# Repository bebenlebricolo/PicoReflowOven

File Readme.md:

# Pico Reflow Oven

My own version of a custom reflow oven, built around my former kitchen oven and whatever was in
the drawers. Hence the "frankenstein" style: this time I'm not sourcing components for a project,
I'm building one from spare parts (plus a few things I still had to order).

I also reused a daughter board from a previous HV project ([NanoFridgeThermostat](https://github.com/bebenlebricolo/NanoFridgeThermostat)),
since it was designed as a self-contained opto-isolated triac switching board. A revisited
schematic for this project lives in `Electronics/PicoReflowOven/`.

## What is it for?

Reflowing custom PCBs in a 1500 W / 230 V convection oven that already has a high-temperature fan
and 2 sets of heating elements (top + bottom) — forced convection keeps the heat distribution as
even as possible.

- **Main target:** low-temp paste **Sn42Bi58** (melts at 138 °C, peak 170–180 °C)
- **Secondary target:** standard **SAC305 / SnAgCu** (peak ~245–250 °C) — reachable by
  disconnecting the original thermal cutout, in "bench" mode only (see Safety)

The stock oven dial goes to ~230 °C but only ever reached ~190–200 °C; measured ramp is
~0.6–0.67 °C/s, and the real fight is the **overshoot at the peak**, not the climb. Full analysis:
`Docs/DesignDeepDive.md`.

## Philosophy

Reuse parts, and keep the oven revertible to its stock configuration with minimal modifications
(original front panel and controls stay; a 2-pin connector restores the stock wiring in ~30 s).
Based on the stock configuration alone, low-temp paste is already reachable — what was missing is
a live temperature reading, a way to switch the elements, and an alarm to open the door.

## Safety (summary — the full architecture is part of the design, don't bypass it)

This project switches mains AC (230 V). Never touch live components. **No fuse, no thermal fuse**
(a shorted triac draws the same current as the load — no fuse would see it), so bounding is:

1. **Autonomous mode (SnBi only, default):** the original thermal cutout stays in series
   (~210–220 °C, above the 180 °C SnBi peak, independent of the Pico and triac). It trips below
   the SAC peak — SnBi only.
2. **Bench mode (any SAC run or test > 250 °C, cutout disconnected):** operator present at all
   times, mechanical timer armed, logical cutoffs ~300 °C.
3. **Mechanical timer armed at every run.** After every bench session, physically reconnect the
   cutout before any SnBi run. **SAC = bench mode only.**
4. House rules: thermal checks unplugged at residual heat; no PVC/thermoplastics in the cavity
   gap; HV/LV ≥ 6 mm apart in the enclosure; sacrificial probe bolted through a drilled FR4 plate.

Details: `Docs/DesignDeepDive.md` §3.

## Architecture — 3 layers, one golden rule

**The control loop and all safety mechanisms live on the Pico — the PC never supervises the hot
chain.** A run in progress survives a USB disconnect; PC/Bluetooth links are passive observers
(telemetry, settings, launch). Link loss mid-run = the run continues.

```
┌─────────────────────────────────────────────┐
│  Layer 3 — Local HMI                        │
│  SSD1306 OLED 128×64 + rotary encoder       │
│  + 2 buttons (Edit / Back)                  │
├─────────────────────────────────────────────┤
│  Layer 2 — USB protocol (CDC /dev/ttyACM0)  │
│  Commands: PROFILE, START, ABORT, GAINS,    │
│  MODE MANUAL x% · Telemetry CSV 1 Hz        │
├─────────────────────────────────────────────┤
│  Layer 1 — Autonomous control + safety      │
│  State machine RAMP/SOAK/PEAK/COOL/ALARM    │
│  PID 1 Hz on board probe · slow PWM         │
│  Interlocks, logical cutoffs                │
└─────────────────────────────────────────────┘
```

Layer 1 runs standalone (no PC, no HMI needed). Hardware, pinout (reference: the KiCad schematic),
measurement and protocol specs: `Docs/DesignDeepDive.md` and `Firmware/Readme.md`.

## Profiles

**SnBi first — the daily driver:**

| Phase | Setpoint |
|-------|----------|
| Free ramp | ~0.6 °C/s up to ~145 °C |
| Soak | 145–150 °C, 60–90 s |
| Peak | 170–180 °C |
| TAL | 30–60 s above 138 °C |
| Cooling | Door open + convection fan |

**SAC305 — later, bench mode only** (values [DATASHEET]): free ramp ~1–2 °C/s target to ~150 °C,
soak 150–180 °C 60–120 s, peak 245–250 °C, TAL 30–60 s above 217 °C, same cooling.

The profile table is extensible (paste alloy × board thermal mass) — not a hard-coded list.

## Using it

- **From the box:** OLED + encoder + Edit/Back. Edit = validate/START, Back = cancel; once
  running, the field becomes STOP and either button stops immediately.
- **From a Linux PC:** `/dev/ttyACM0` (native CDC, no reset on open — capture can start mid-cycle).
  Line protocol: `PROFILE <name>`, `START`, `ABORT`, `GAINS kp ki kd`, `MODE MANUAL x%`;
  1 Hz CSV telemetry `t,sp,tc_board,tc_air,duty,STATE` (e.g. `cat /dev/ttyACM0 | tee run.csv`).
  Group `dialout`; disable ModemManager. Nothing is logged before the port is opened. Spec:
  `Firmware/Readme.md`.
---

## Repo layout

```
PicoReflowOven/
├── Readme.md                  ← you are here
├── AGENTS.md                  ← rules for AI agents working in this repo
├── Docs/
│   ├── InitialContext.md      ← full project write-up (Nov 2026, FR) — decision source of truth
│   └── DesignDeepDive.md      ← technical deep dive (oven analysis, safety, pinout, protocol…)
├── Electronics/
│   ├── Readme.md              ← HT daughter board, triac, wiring, BOM
│   └── PicoReflowOven/        ← KiCad schematic + PCB (pinout reference)
└── Firmware/
    └── Readme.md              ← firmware layers, pinout, USB protocol
```

## Where we're at (Nov 2026)

- [x] Design frozen (safety architecture, triac choice, pinout per KiCad schematic)
- [ ] Wiring the power section + protections
- [ ] Firmware generation (layer 1 → 2 → 3)
- [ ] No-load runs (`MODE MANUAL 100` 20–30 min → unplugged thermal check → heatsink ≤ 70 °C)
- [ ] Calibration (probe in 3 positions), profile runs with PC plot, PID tuning
- [ ] First real reflow, logged

Still [OPEN]: SAC ramp near 250 °C (measure on first bench run) · SAC bench-only decision to be
logged as DEC-XXX · TME delivery checks (Kapton adhesive = silicone, TKD wire ≥ 1 mm², triac =
BTA316Y) · blower-on-cutout idea under exploration (see `Docs/DesignDeepDive.md` §1.1).

Later, maybe: re-insulate with rock wool (encapsulated) for a faster ramp and higher ceiling.

## Disclaimer

This thing plugs into the wall (230 V) and runs hot. Build at your own risk — the safety
architecture above is part of the design, don't bypass it.

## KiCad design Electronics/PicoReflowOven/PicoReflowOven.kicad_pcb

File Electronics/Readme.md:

# Electronics

This folder is the home of the Electronics designs (schematics, PCBs, BOM, wiring).

The low-voltage control board schematic lives in [`PicoReflowOven/PicoReflowOven.kicad_sch`](PicoReflowOven/PicoReflowOven.kicad_sch) (KiCad 10) — it is the **as-built source of truth for the pinout** (see the pinout tables in the root `Readme.md` and `Firmware/Readme.md`). Regenerate the netlist with `kicad-cli sch export netlist`.

The power section reuses a daughter board from the **NanoFridgeThermostat** project and drives a **230 V / 1500 W** convection oven through a triac. All design decisions below are frozen — see `Docs/InitialContext.md` for the full rationale.

---

## HT Daughter Board (reused from NanoFridgeThermostat)

Reusing the HT Daughter board from [NanoFridgeThermostat:](https://github.com/bebenlebricolo/NanoFridgeThermostat)
| Item | Value |
|------|-------|
| Opto-triac | **MOC3042M** (zero-cross detection built in) |
| Snubber | R4 360 Ω + C1 10 nF / 500 V AC |
| Terminals | TE 5.08 mm |
| Headers | J5 = `TriacDriverEnable`, J6 = LED return (2.54 mm) |
| R8 | 330 Ω (unchanged — design point: limits MOC peak current to 1 A) |

**J6 is no longer ground** — it is the switched LED return. At rest, J6 measures ~5 V; that is normal, not a fault.

---

## Triac

| | Phase 1 (validation only) | Final |
|---|---|---|
| Part | FT0814MH | **BTA316Y-800CTQ** (WeEn) |
| Rating | 8 A / 600 V, bare tab | 16 A / 800 V, **IITO-220 factory-isolated tab** (2500 V RMS) |
| IGT | 35 mA, 3Q | 35 mA, 3Q Hi-Commutation — drop-in proven |
| Isolation | Mica kit mandatory (SMICA-TO220-2 + NIPPEL-TO220), nylon screw or insulating shoulder — the screw passes through tab AND plate | None needed — tab is isolated; plate and enclosure never live |

TO-220 pinout: 1 = MT1, 2 = MT2, 3 = G.

Dissipation at 6.5 A: ~7.5–8.5 W → heatsink required, target Rth ≤ 3 °C/W. Tj ≈ 75 °C at full power on plate/heatsink in airflow.

**Heatsink candidates** (empirical test: `MODE MANUAL 100` for 20–30 min, base ≤ 70 °C wins):
- Alu plate 100×100 mm (salvaged)
- Fischer SK610-84AL
- Alutronic PR33/25.4/SE

Mount vertically, air on both faces, thermal paste, moderate screw torque.

---

## Opto Drive — NPN Low-Side (retained pattern)

> **The GPIO is a signal, not a source.**

LED chain: `5V_EXT → 330 Ω → J5 → MOC3042 LED → J6 → NPN collector → emitter → GND`

- Base driven by **GP15** via 2.2–4.7 kΩ, **10 kΩ pull-down** (Hi-Z at boot = explicit OFF)
- Base current ~1 mA — default 4 mA GPIO is enough, no drive strength needed
- LED ~11.4 mA on the 5V_EXT rail → **zero I/O budget** on the Pico (total budget ≈ 10 mA, no brown-out risk)
- Non-inverting: GP15 high = heat
- Any salvaged NPN: BC547 / 2N3904 / 2N2222
- Same NPN pattern for buzzer (GP8, base via 1 kΩ) and optional case fan (GP6, base via 470 Ω + 10 k pull-down)
- Check J5 polarity with a multimeter (diode mode, ~1.1 V forward)

---

## Mains Chain

```
Wall socket → mechanical timer → original thermal cutout (autonomous mode)
  → cable gland → J2 → triac → J3 → cable gland → heating elements
```

- Flexible 1.5 mm², crimped ferrules, cable ties
- **Convection fan powered continuously, outside the triac loop** (direct phase from the timer)
- PCB traces (IPC-2221, 1 oz): phase 4 mm, neutral 5.8 mm

---

## Wiring & Cables

| Zone | Cable | Notes |
|------|-------|-------|
| Cavity gap (inside shell) | **LAPP ÖLFLEX HEAT 350 SC 1.5 mm²** (glass fiber, 350 °C) or factory wire rated 250 °C+ | **Crimp (nickel core), never solder** — tin melts at 230 °C. Silicone 180 °C forbidden here. Alt: PTFE 260 °C (ÖLFLEX HEAT 260 SC) |
| Outside | Silicone 180 °C, 1.5 mm² (TKD) — verify cross-section ≥ 1 mm² at delivery |
| Element terminals | Bare spade terminal + Kapton with **silicone adhesive** (~280 °C) or PTFE heat-shrink 260 °C | Standard acrylic adhesive peels at ~155 °C |

- PVC-to-factory-wire junction **outside** the shell, crimped splice in a closed box; cable glands on the outside (BM4007 PG7, IP68)
- Every splice under glass-fiber sleeving
- Drill the shell as close as possible to the element terminals; 2-pin inline connector on the element supply (return to stock config in 30 s)

### 9 assembly reflexes
1. Cable gland + 1.5 mm² flexible outside only, crimped ferrules
2. No PVC in the cavity gap
3. Phase junctions outside the shell, in a closed box
4. Convection fan outside the triac loop
5. Triac tab: moderate torque + paste (BTA isolated = plate not live)
6. HV/LV separation ≥ 6 mm, airflow through heatsink
7. Open the serial capture **before** starting the cycle
8. First thermal check with power off, at residual heat
9. Timer armed at every run + cutout reconnected after bench

### No-load test before reassembly
1. Timer OFF → ohmmeter on the loop (continuity timer → cutout → elements ≈ 35 Ω; triac blocked = open circuit)
2. `MODE MANUAL 100` for 20–30 min
3. Unplug at the wall → residual-heat check (triac/plate, terminals, cable glands, cable against sheet metal)

---

## BOM

### In stock
Pico · NanoFridgeThermostat daughter board · FT0814MH (phase 1) · 2× K probes + MAX6675 · encoders, buttons, LED · SSD1306 OLED · 10 A relay (backup) · HC-05 + HC-06 · 100×100 alu plate · USB charger 1 A · salvaged NPN · prototyping boards

### TME order (Nov 2026, ~41 € TTC)

| Item | Qty | Role |
|------|-----|------|
| Triac **BTA316Y-800CTQ** (the Y = isolated tab) | ×5 | switching + lifetime spares |
| LAPP ÖLFLEX HEAT 350 SC 1.5 mm² | 2 m | cavity gap, crimp |
| Polyimide tape IPT POL-12MM 12 mm × 33 m | 1 | Kapton — **verify silicone vs acrylic adhesive** |
| Ninigi SMICA-TO220-2 (mica) + NIPPEL-TO220 | ×10 each | phase-1 isolation kit (FT0814MH bare tab) |
| Heatsinks Fischer SK610-84AL + Alutronic PR33/25.4/SE | 1 + 1 | candidates vs salvaged alu plate |
| Cable glands BM4007 (PG7, IP68) | ×5 | shell outlet |
| 1N5819 Schottky | ×5 | power supply |
| TKD silicone cable 2 colors | 2×1 m | outside — **verify ≥ 1 mm²** |

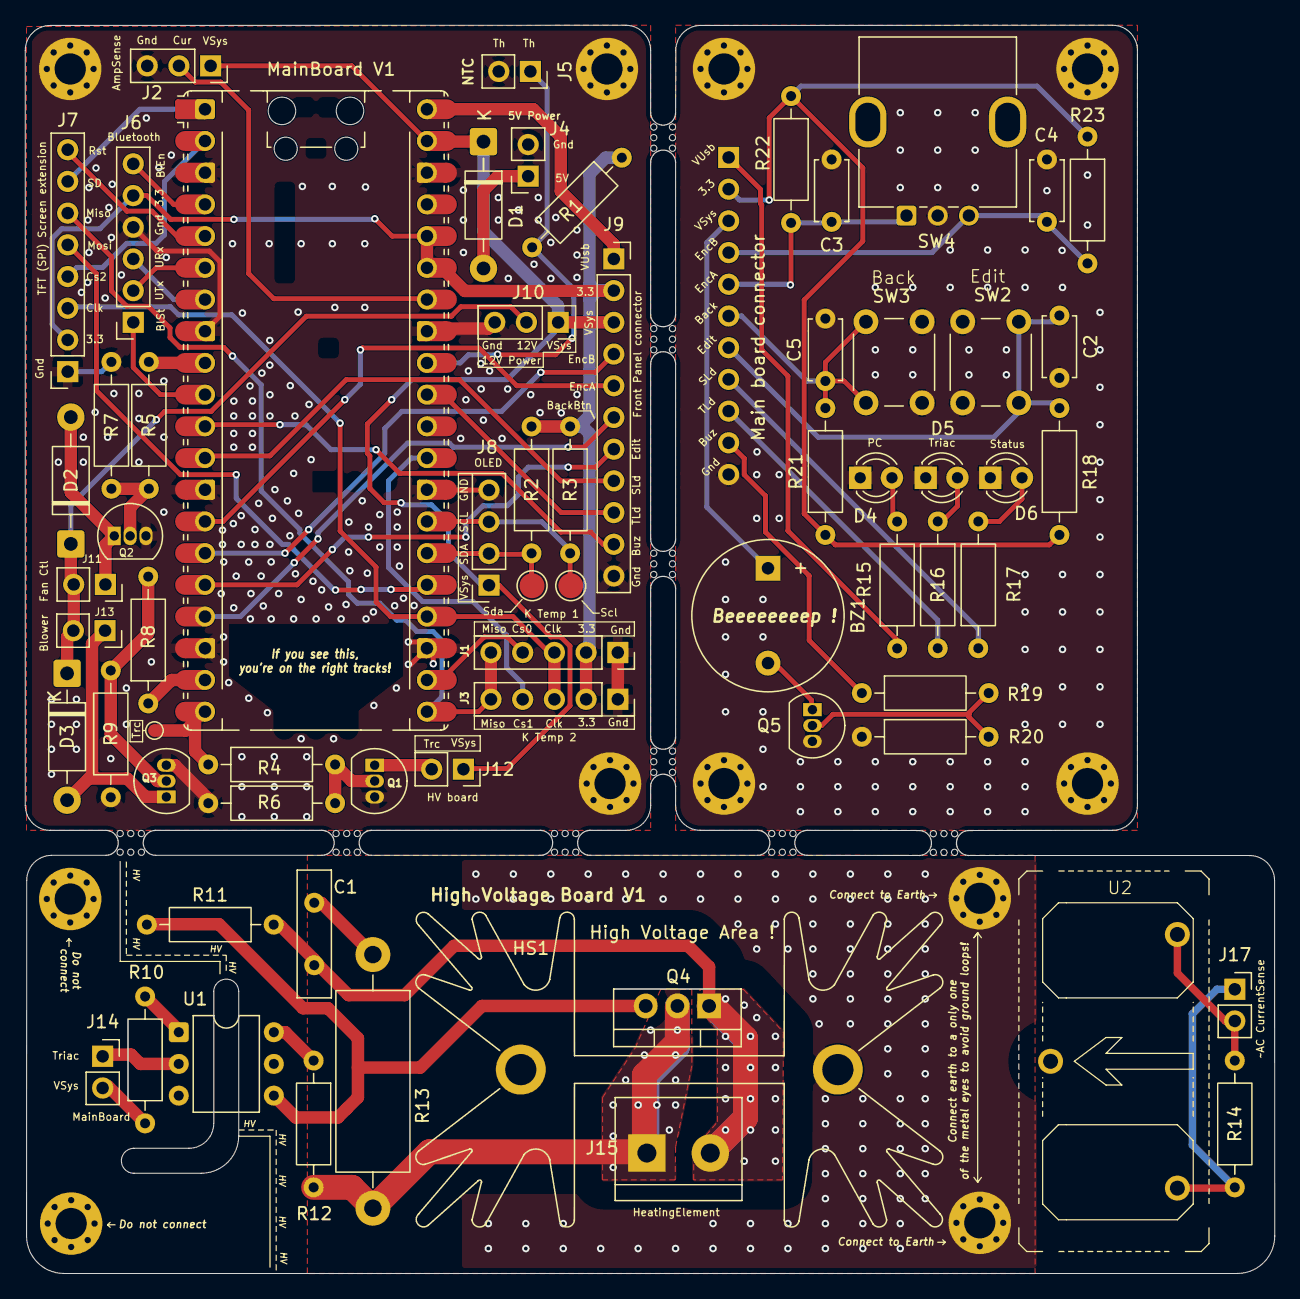
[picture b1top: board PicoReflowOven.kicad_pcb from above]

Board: 2 copper layers, 100.1 x 100.0 mm, 78 parts (1 on the bottom side), 65 nets.

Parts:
A1: RaspberryPi_Pico; RaspberryPi_Pico_Common_Unspecified
BZ1: Buzzer; Buzzer_12x9.5RM7.6
C1: 10n / 500V+ AC; C_Disc_D10.0mm_W2.5mm_P5.00mm
C2, C3, C4, C5: 100n; C_Disc_D4.7mm_W2.5mm_P5.00mm
D1, D2, D3: 1N5819; D_DO-41_SOD81_P10.16mm_Horizontal
D4: UsbPowerLed; LED_D3.0mm
D5: TriacStatusLed; LED_D3.0mm
D6: StatusLed; LED_D3.0mm
H1, H2, H3, H4, H5, H6, H7, H8, H9, H10, H11: MountingHole_Pad; MountingHole_2.5mm_Pad_Via
HS1: PR33/25,4/SE; Heatsink_Fischer_SK129-STS_42x25mm_2xDrill2.5mm
J1: TempProbe1Con; PinSocket_1x05_P2.54mm_Vertical
J2: CurrentSensingBoardCon; PinSocket_1x03_P2.54mm_Vertical
J3: TempProbe2Con; PinSocket_1x05_P2.54mm_Vertical
J4: PowerCon; PinSocket_1x02_P2.54mm_Vertical
J5: ThermistorCon; PinSocket_1x02_P2.54mm_Vertical
J6: BL HC-05 Con; PinSocket_1x06_P2.54mm_Vertical
J7: SPI Display; PinSocket_1x08_P2.54mm_Vertical
J8: OLED Display; PinSocket_1x04_P2.54mm_Vertical
J9: FrontPanelMCUCon; PinSocket_1x11_P2.54mm_Vertical
J10: BoostModuleCon; PinSocket_1x03_P2.54mm_Vertical
J11: CaseFanConn; PinSocket_1x02_P2.54mm_Vertical
J12, J14: TriacConn; PinSocket_1x02_P2.54mm_Vertical
J13: ThermostatBlowerConn; PinSocket_1x02_P2.54mm_Vertical
J15: HeatingElementConn; TE-282836-2-5.08mm
J16: FrontPanelCon; PinHeader_1x11_P2.54mm_Vertical
J17: AcCurrentSensingCon; PinSocket_1x02_P2.54mm_Vertical
Q1, Q2, Q3, Q5: BC337; TO-92_Inline
Q4: BTA316Y-800CTQ; TO-220-3_Vertical
R1: 47k; R_Axial_DIN0207_L6.3mm_D2.5mm_P10.16mm_Horizontal
R2, R3, R15: 4.7k; R_Axial_DIN0207_L6.3mm_D2.5mm_P10.16mm_Horizontal
R4, R5, R8, R18, R19, R21, R22, R23: 1k; R_Axial_DIN0207_L6.3mm_D2.5mm_P10.16mm_Horizontal
R6, R7, R9, R20: 10k; R_Axial_DIN0207_L6.3mm_D2.5mm_P10.16mm_Horizontal
R10, R11, R16, R17: 330; R_Axial_DIN0207_L6.3mm_D2.5mm_P10.16mm_Horizontal
R12: 360; R_Axial_DIN0207_L6.3mm_D2.5mm_P10.16mm_Horizontal
R13: 330Ω / 1W; R_Axial_DIN0614_L14.3mm_D5.7mm_P20.32mm_Horizontal
R14: 100Ω /0,25W; R_Axial_DIN0207_L6.3mm_D2.5mm_P10.16mm_Horizontal
SW2: EditBtn; SW_PUSH_6mm
SW3: BackBtn; SW_PUSH_6mm
SW4: RotaryEncoder; RotaryEncoder_Bourns_Vertical_PEC12R-3x17F-Nxxxx
TP1, TP2: TestPoint; TestPoint_Pad_D2.0mm
TP3: TestPoint; TestPoint_Pad_D1.0mm
U1: MOC3042M; DIP-6_W7.62mm
U2: CT-RSPRO-1243888

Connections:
/HighVoltageBoard/HV/CurrentSense1: J17.1, R14.1, U2.1 (A)
/HighVoltageBoard/HV/CurrentSense2: J17.2, R14.2, U2.2 (B)
/HighVoltageBoard/HV/OptoGate: Q4.3 (G), R11.2, U1.4
/HighVoltageBoard/HV/OptoLive: R12.1, U1.6
/HighVoltageBoard/HeatingElemWire1: J15.1, Q4.2 (A2), R12.2, R13.2
/HighVoltageBoard/HeatingElemWire2: C1.2, J15.2, Q4.1 (A1), R11.1
/HighVoltageBoard/LV/OptoLedIn: R10.2, U1.1
/HighVoltageBoard/SnubberResLow: C1.1, R13.1
/HighVoltageBoard/TriacLowSideSwitch: J14.1, U1.2
/HighVoltageBoard/VSys: J14.2, R10.1
/MainBoard/3.3V: A1.35 (ADC_VREF), A1.36 (3V3), J1.2, J3.2, J6.5, J7.2, J9.2, R1.2, R2.1, R3.1
/MainBoard/5VCharger: D1.2 (A), J4.1
/MainBoard/12VDC: D2.1 (K), D3.1 (K), J10.2, J11.2, J13.2
/MainBoard/BL_ENABLE: A1.4 (GPIO2), J6.6
/MainBoard/BL_STATE: A1.10 (GPIO7), J6.1
/MainBoard/BackButton: A1.17 (GPIO13), J9.6
/MainBoard/BlowerFan: A1.19 (GPIO14), R8.1
/MainBoard/BlowerReturn: D3.2 (A), J13.1, Q3.1 (C)
/MainBoard/Buzzer: A1.11 (GPIO8), J9.10
/MainBoard/CaseFan: A1.9 (GPIO6), R5.1
/MainBoard/CurrentSensing: A1.34 (GPIO28_ADC2), J2.2
/MainBoard/EditButton: A1.16 (GPIO12), J9.7
/MainBoard/EncoderA: A1.14 (GPIO10), J9.5
/MainBoard/EncoderB: A1.15 (GPIO11), J9.4
/MainBoard/FanReturn: D2.2 (A), J11.1, Q2.1 (C)
/MainBoard/FrontPanel/3.3V: J16.2, R18.1, R21.1, R22.1, R23.1
/MainBoard/FrontPanel/BackButton: C5.1, J16.6, R21.2, SW3.2
/MainBoard/FrontPanel/Buzzer: J16.10, R19.1
/MainBoard/FrontPanel/EditButton: C2.1, J16.7, R18.2, SW2.2
/MainBoard/FrontPanel/EncoderA: C3.1, J16.5, R22.2, SW4.A
/MainBoard/FrontPanel/EncoderB: C4.2, J16.4, R23.2, SW4.B
/MainBoard/FrontPanel/Status: D6.2 (A), R17.2
/MainBoard/FrontPanel/StatusLed: J16.8, R17.1
/MainBoard/FrontPanel/TriacStat: D5.2 (A), R16.1
/MainBoard/FrontPanel/TriacStatusLed: J16.9, R16.2
/MainBoard/FrontPanel/UsbPower: D4.2 (A), R15.2
/MainBoard/FrontPanel/VBusUsbPC: J16.1, R15.1
/MainBoard/FrontPanel/VSys: BZ1.1 (+), J16.3
/MainBoard/I2C_SCL: A1.27 (GPIO21), J8.3, R3.2, TP2.1 (1_1)
/MainBoard/I2C_SDA: A1.26 (GPIO20), J8.2, R2.2, TP1.1 (1_1)
/MainBoard/SPI_CLK: A1.24 (GPIO18), J1.3, J3.3, J7.3
/MainBoard/SPI_CS0: A1.22 (GPIO17), J1.4
/MainBoard/SPI_CS1: A1.29 (GPIO22), J3.4
/MainBoard/SPI_CS2: A1.2 (GPIO1), J7.4
/MainBoard/SPI_MISO: A1.21 (GPIO16), J1.5, J3.5, J7.6
/MainBoard/SPI_MOSI: A1.25 (GPIO19), J7.5
/MainBoard/StatusLed: A1.12 (GPIO9), J9.8
/MainBoard/TFT_RESET: A1.5 (GPIO3), J7.8
/MainBoard/TFT_SD: A1.1 (GPIO0), J7.7
/MainBoard/Thermistor: A1.32 (GPIO27_ADC1), J5.1, R1.1
/MainBoard/TriacDriver: A1.20 (GPIO15), R4.1, TP3.1 (1_1)
/MainBoard/TriacLowSideSwitch: J12.2, Q1.1 (C)
/MainBoard/TriacStatusLed: A1.31 (GPIO26_ADC0), J9.9
/MainBoard/UART_RX: A1.7 (GPIO5), J6.3
/MainBoard/UART_TX: A1.6 (GPIO4), J6.2
/MainBoard/VBusUsbPC: A1.40 (VBUS), J9.1
/MainBoard/VSys: A1.39 (VSYS), D1.1 (K), J2.1, J8.1, J9.3, J10.1, J12.1
Earth: H4.1 (1_1), H5.1 (1_1), HS1.1
GND: A1.3 (GND), A1.8 (GND), A1.13 (GND), A1.18 (GND), A1.23 (GND), A1.28 (GND), A1.33 (AGND), A1.38 (GND), H1.1 (1_1), H2.1 (1_1), H3.1 (1_1), J1.1, J2.3, J3.1, J4.2, J5.2, J6.4, J7.1, J8.4, J9.11, J10.3, Q1.3 (E), Q2.3 (E), Q3.3 (E), R6.1, R7.1, R9.1
GNDREF: C2.2, C3.2, C4.1, C5.2, D4.1 (K), D5.1 (K), D6.1 (K), H8.1 (1_1), H9.1 (1_1), H10.1 (1_1), H11.1 (1_1), J16.11, Q5.3 (E), R20.1, SW2.1, SW3.1, SW4.C
unnamed: BZ1.2 (-), Q5.1 (C)
unnamed: Q1.2 (B), R4.2, R6.2
unnamed: Q2.2 (B), R5.2, R7.2
unnamed: Q3.2 (B), R8.2, R9.2
unnamed: Q5.2 (B), R19.2, R20.2

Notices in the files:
Electronics/PicoReflowOven/PicoReflowOven.kicad_pcb:
CERN OHL-V2
